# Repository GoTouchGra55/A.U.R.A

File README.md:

# 🚧 Under Active Development 🚧

# 

### A **flight computer** to do met- I mean math for a **rocket** (*Supposedly for a self-landing rocket*).

I had a lot of fun designing this project, though there may still be a few mistakes here and there, so forgive me for that

Feel free to suggest improvements, modify the design, or contribute your own ideas to the project as well!

---

# PCB Preview

### Yes, its 4 layers ;3

---

# Schematics

---

# Extra Info

1. **Use a 2s LiPo battery** if you decide to use this board in your project. **Discard the battery if it smells "funny".**

2. **Check for any damage on the pcb** as it can be the reason for a **catastrophic failure**.

3. **USE A 915MHz SMA ANTENNA ONLY!** Others will work fine but you'll spend a while wondering about the poor range.

---

# Bill Of Materials

### See [BOM](Gravitas-bom.csv)

---

# License

### MIT License - see [LICENSE](LICENSE)

---

# Author

### **Shaurya Tamang**
Contact: shauryatamang.dev@gmail.com

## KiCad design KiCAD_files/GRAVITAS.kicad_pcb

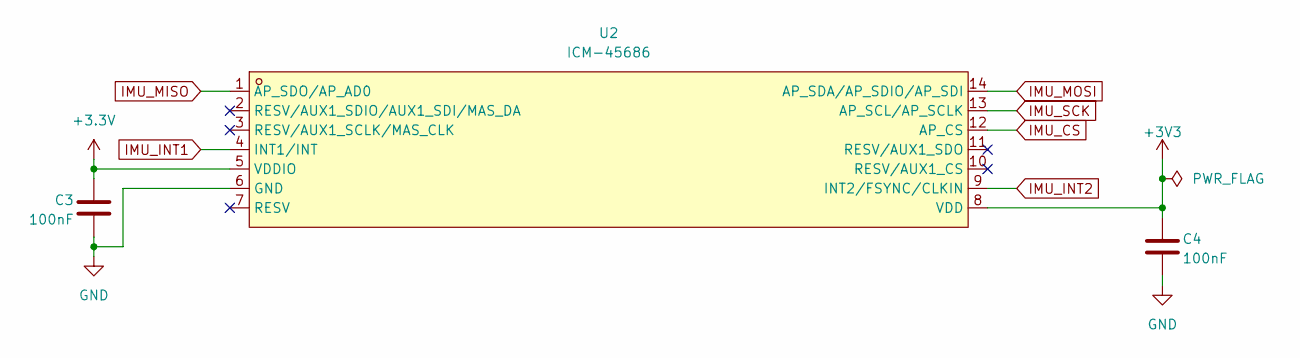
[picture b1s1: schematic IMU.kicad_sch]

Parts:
C3, C4: 100nF; C_0402_1005Metric
U2: ICM-45686; IC_ICM-45686; LCSC Part C22459454

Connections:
+3.3V: C3.1, U2.5 (VDDIO); also elsewhere on the board
+3V3: C4.1, U2.8 (VDD)
IMU_CS: U2.12 (AP_CS); also elsewhere on the board
IMU_INT1: U2.4 (INT1/INT); also elsewhere on the board
IMU_INT2: U2.9 (INT2/FSYNC/CLKIN); also elsewhere on the board
IMU_MISO: U2.1 (AP_SDO/AP_AD0); also elsewhere on the board
IMU_MOSI: U2.14 (AP_SDA/AP_SDIO/AP_SDI); also elsewhere on the board
IMU_SCK: U2.13 (AP_SCL/AP_SCLK); also elsewhere on the board

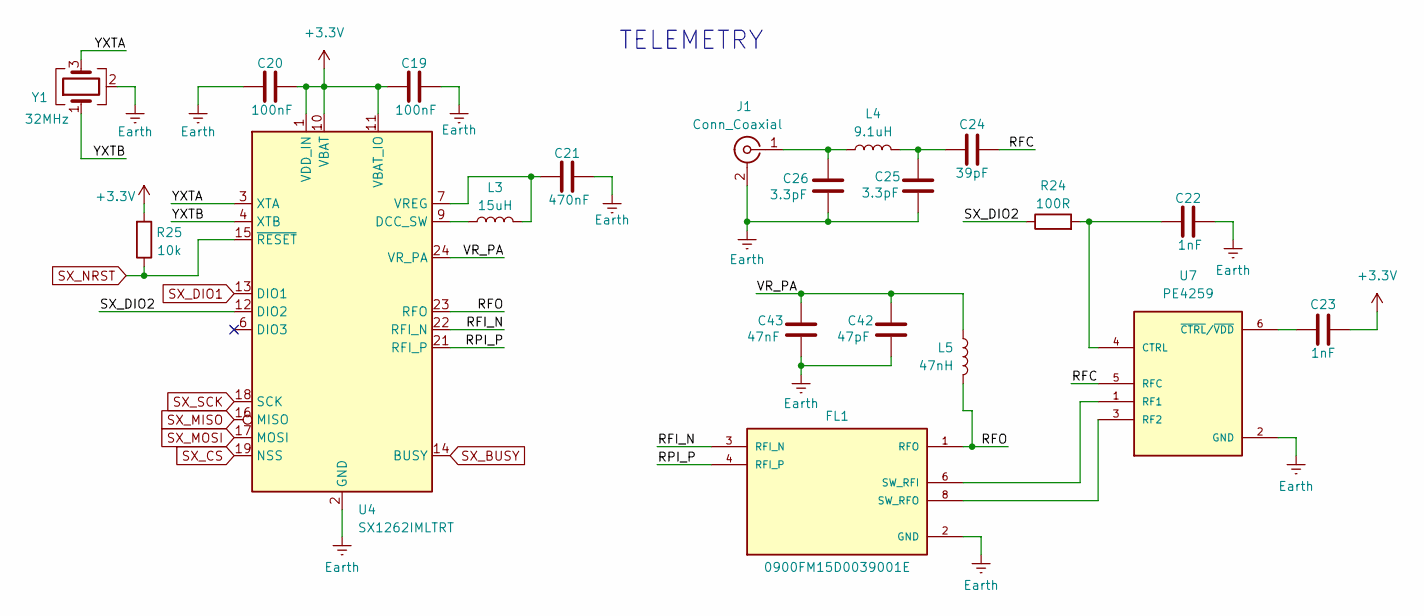
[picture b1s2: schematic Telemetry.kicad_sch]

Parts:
C19, C20: 100nF; C_0402_1005Metric
C21: 470nF; C_0402_1005Metric
C22, C23: 1nF; C_0603_1608Metric
C24: 39pF; C_0402_1005Metric
C25, C26: 3.3pF; C_0402_1005Metric
C42: 47pF; C_0402_1005Metric
C43: 47nF; C_0402_1005Metric
FL1: 0900FM15D0039001E; FIL_0900FM15D0039001E; PARTREV 2.0
J1: Conn_Coaxial; SMA_Amphenol_132134-10_Vertical
L3: 15uH; L_Cenker_CKCS4030
L4: 9.1uH; L_Changjiang_FNR5020S
L5: 47nH; L_0201_0603Metric
R24: 100R; R_0603_1608Metric
R25: 10k; R_0603_1608Metric
U4: SX1262IMLTRT; QFN-24-1EP_4x4mm_P0.5mm_EP2.6x2.6mm
U7: PE4259; SOT65P215X110-6N
Y1: 32MHz; Crystal_SMD_3225-4Pin_3.2x2.5mm

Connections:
+3.3V: C19.1, C20.2, C23.2, R25.2, U4.1 (VDD_IN), U4.10 (VBAT), U4.11 (VBAT_IO); also elsewhere on the board
/Telemetry/RFC: C24.1, U7.5 (RFC)
/Telemetry/RFI_N: FL1.3 (RFI_N), U4.22 (RFI_N)
/Telemetry/RFO: FL1.1 (RFO), L5.1, U4.23 (RFO)
/Telemetry/RPI_P: FL1.4 (RFI_P), U4.21 (RFI_P)
/Telemetry/SX_DIO2: R24.1, U4.12 (DIO2)
/Telemetry/VR_PA: C42.1, C43.1, L5.2, U4.24 (VR_PA)
/Telemetry/YXTA: U4.3 (XTA), Y1.3
/Telemetry/YXTB: U4.4 (XTB), Y1.1
unnamed: C24.2, C25.2, L4.1
unnamed: FL1.6 (SW_RFI), U7.1 (RF1)
unnamed: FL1.8 (SW_RFO), U7.3 (RF2)
unnamed: C26.2, J1.1 (In), L4.2
unnamed: L3.1, U4.9 (DCC_SW)
unnamed: C21.1, L3.2, U4.7 (VREG)
unnamed: C22.1, R24.2, U7.4 (CTRL)
unnamed: C23.1, U7.6 (~CTRL/~VDD)
SX_BUSY: U4.14 (BUSY); also elsewhere on the board
SX_CS: U4.19 (NSS); also elsewhere on the board
SX_DIO1: U4.13 (DIO1); also elsewhere on the board
SX_MISO: U4.16 (MISO); also elsewhere on the board
SX_MOSI: U4.17 (MOSI); also elsewhere on the board
SX_NRST: R25.1, U4.15 (~RESET); also elsewhere on the board
SX_SCK: U4.18 (SCK); also elsewhere on the board

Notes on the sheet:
TELEMETRY

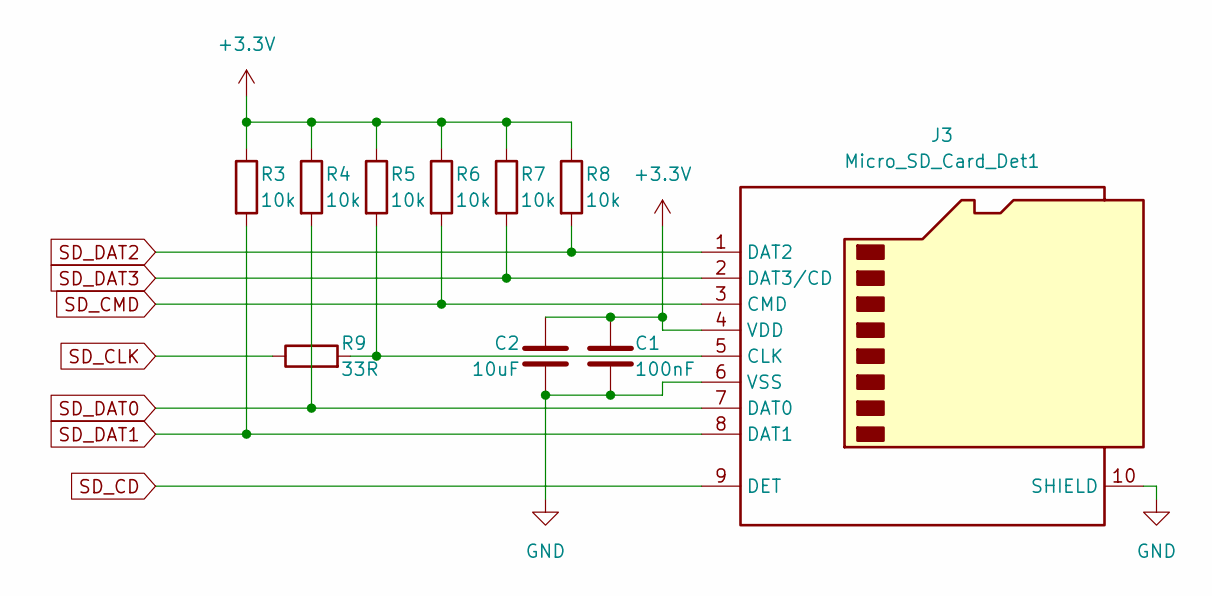
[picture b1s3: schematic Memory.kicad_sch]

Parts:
C1: 100nF; C_0402_1005Metric
C2: 10uF; C_0805_2012Metric
J3: Micro_SD_Card_Det1; microSD_HC_Molex_47219
R3, R4, R5, R6, R7, R8: 10k; R_0603_1608Metric
R9: 33R; R_0603_1608Metric

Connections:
+3.3V: C1.1, C2.1, J3.4 (VDD), R3.1, R4.1, R5.1, R6.1, R7.1, R8.1; also elsewhere on the board
unnamed: J3.5 (CLK), R5.2, R9.2
SD_CD: J3.9 (DET); also elsewhere on the board
SD_CLK: R9.1; also elsewhere on the board
SD_CMD: J3.3 (CMD), R6.2; also elsewhere on the board
SD_DAT0: J3.7 (DAT0), R4.2; also elsewhere on the board
SD_DAT1: J3.8 (DAT1), R3.2; also elsewhere on the board
SD_DAT2: J3.1 (DAT2), R8.2; also elsewhere on the board
SD_DAT3: J3.2 (DAT3/CD), R7.2; also elsewhere on the board

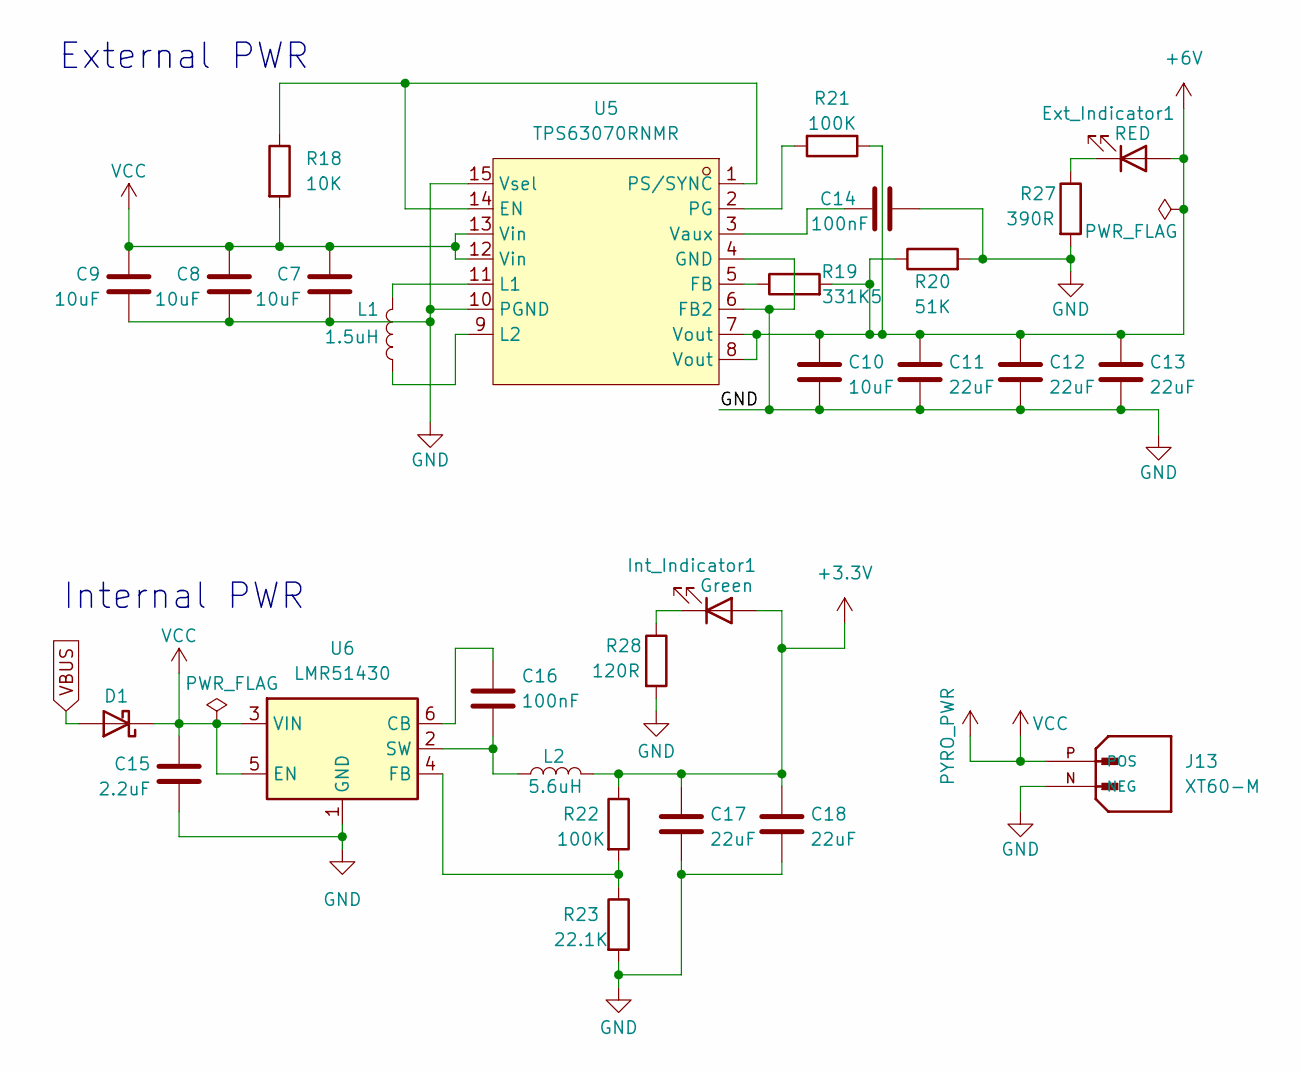
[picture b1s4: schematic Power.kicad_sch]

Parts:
C7, C8, C9, C10: 10uF; C_0805_2012Metric
C11, C12, C13: 22uF; C_0805_2012Metric
C14, C16: 100nF; C_0402_1005Metric
C15: 2.2uF; C_0603_1608Metric
C17, C18: 22uF; C_0603_1608Metric
D1: D_Schottky; D_SOD-123
Ext_Indicator1: RED; LED_0402_1005Metric
Int_Indicator1: Green; LED_0402_1005Metric
J13: XT60-M; AMASS_XT60-M; PARTREV V1.2
L1: 1.5uH; L_Cenker_CKCS4018
L2: 5.6uH; L_Cenker_CKCS3015
R18: 10K; R_0603_1608Metric
R19: 331K5; R_0603_1608Metric
R20: 51K; R_0603_1608Metric
R21, R22: 100K; R_0603_1608Metric
R23: 22.1K; R_0603_1608Metric
R27: 390R; R_0603_1608Metric
R28: 120R; R_0603_1608Metric
U5: TPS63070RNMR; VREG_TPS63070RNMR; LCSC Part C109322
U6: LMR51430; SOT-23-6

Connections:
+3.3V: C17.1, C18.1, Int_Indicator1.2 (A), L2.1, R22.1; also elsewhere on the board
+6V: C10.1, C11.1, C12.1, C13.1, Ext_Indicator1.2 (A), R19.2, R20.1, R21.1, U5.7 (Vout), U5.8 (Vout); also elsewhere on the board
unnamed: Ext_Indicator1.1 (K), R27.1
unnamed: Int_Indicator1.1 (K), R28.1
unnamed: R18.1, U5.1 (PS/SYNC), U5.14 (EN)
unnamed: R19.1, U5.5 (FB)
unnamed: L1.1, U5.11 (L1)
unnamed: L1.2, U5.9 (L2)
unnamed: R21.2, U5.2 (PG)
unnamed: C14.1, U5.3 (Vaux)
unnamed: C16.1, U6.6 (CB)
unnamed: R22.2, R23.1, U6.4 (FB)
unnamed: C16.2, L2.2, U6.2 (SW)
PYRO_PWR: C7.1, C8.1, C9.1, C15.1, D1.1 (K), J13.P (POS), R18.2, U5.12 (Vin), U5.13 (Vin), U6.3 (VIN), U6.5 (EN); also elsewhere on the board
VBUS: D1.2 (A); also elsewhere on the board

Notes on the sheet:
Internal PWR
External PWR

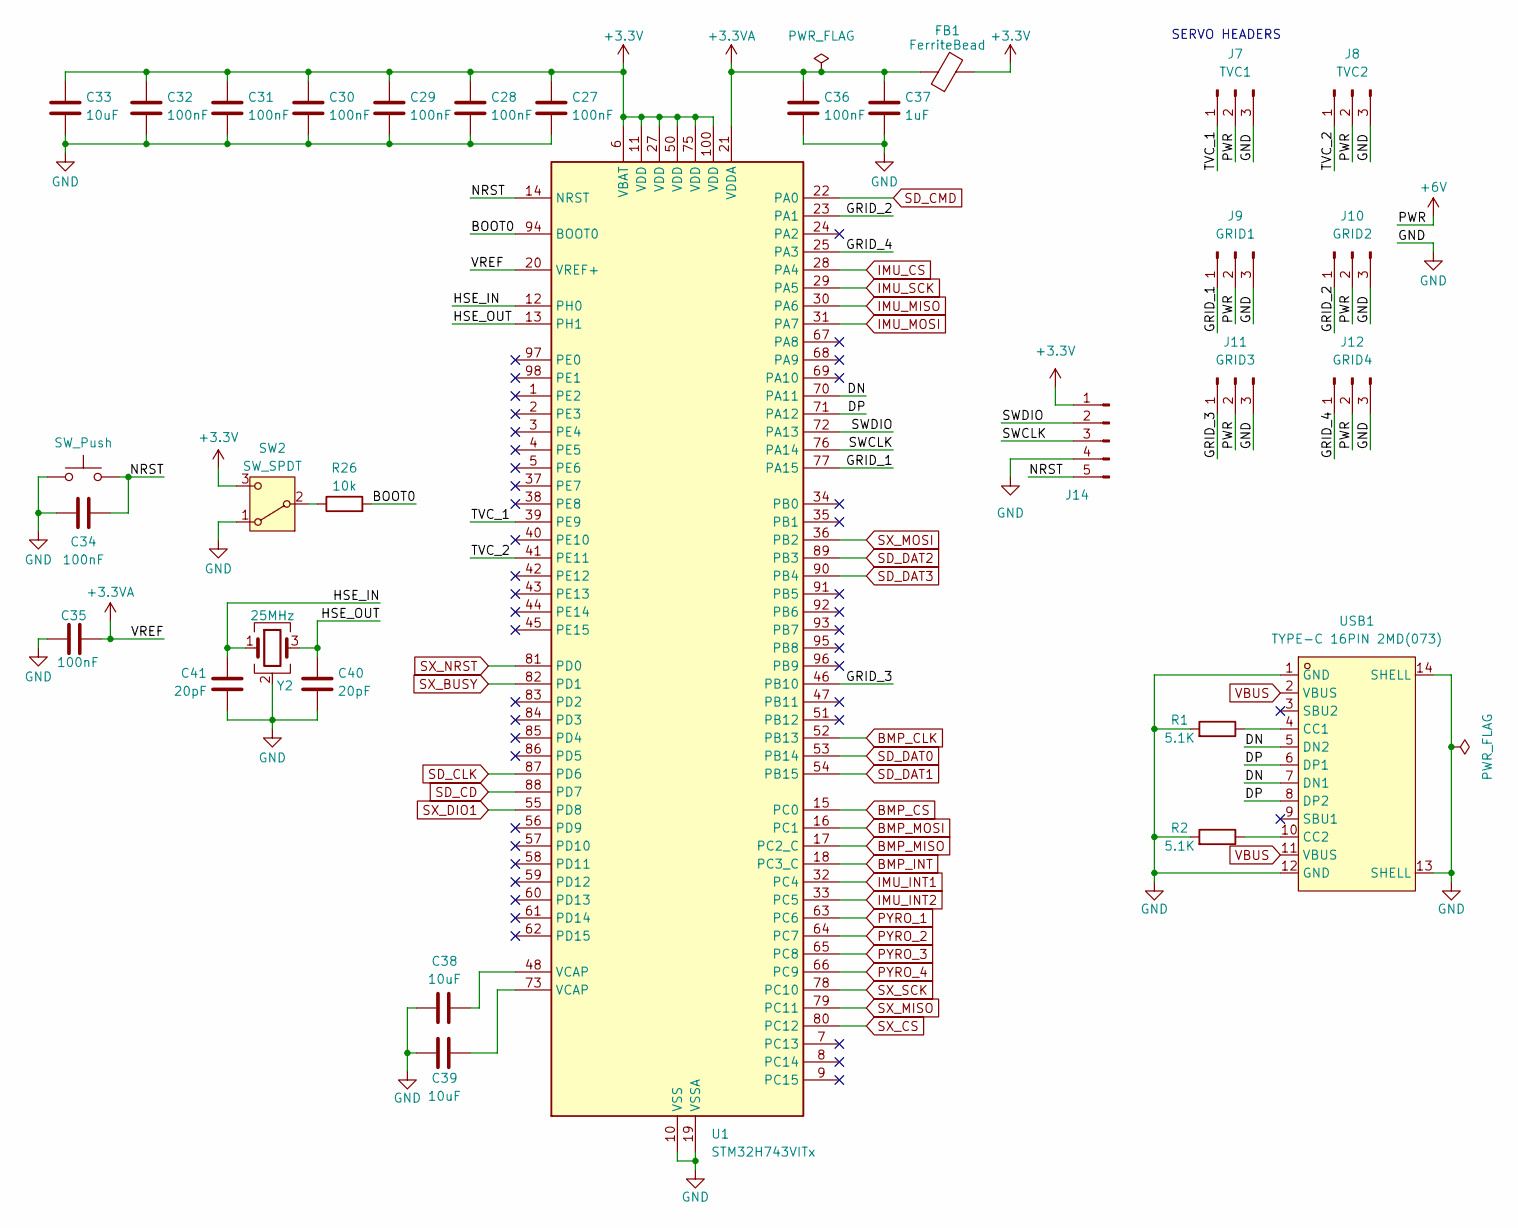
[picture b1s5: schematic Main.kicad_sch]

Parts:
C27, C28, C29, C30, C31, C32, C34, C35, C36: 100nF; C_0402_1005Metric
C33, C38, C39: 10uF; C_0805_2012Metric
C37: 1uF; C_0603_1608Metric
C40, C41: 20pF; C_0402_1005Metric
FB1: FerriteBead; D_0603_1608Metric
J7: TVC1; PinHeader_1x03_P2.54mm_Vertical
J8: TVC2; PinHeader_1x03_P2.54mm_Vertical
J9: GRID1; PinHeader_1x03_P2.54mm_Vertical
J10: GRID2; PinHeader_1x03_P2.54mm_Vertical
J11: GRID3; PinHeader_1x03_P2.54mm_Vertical
J12: GRID4; PinHeader_1x03_P2.54mm_Vertical
J14: Conn_01x05_Pin; JST_EH_S5B-EH_1x05_P2.50mm_Horizontal
R1, R2: 5.1K; R_0603_1608Metric
R26: 10k; R_0603_1608Metric
SW1: SW_Push; SW_SPST_B3S-1000
SW2: SW_SPDT; SW_SPDT_PCM12
U1: STM32H743VITx; LQFP-100_14x14mm_P0.5mm
USB1: TYPE-C 16PIN 2MD(073); HRO_TYPE-C-31-M-12; LCSC Part C2765186
Y2: 25MHz; Crystal_SMD_3225-4Pin_3.2x2.5mm

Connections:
+3.3V: C27.1, C28.1, C29.1, C30.1, C31.1, C32.1, C33.1, FB1.2, J14.1, SW2.3 (C), U1.6 (VBAT), U1.11 (VDD), U1.27 (VDD), U1.50 (VDD), U1.75 (VDD), U1.100 (VDD); also elsewhere on the board
+3.3VA: C35.1, C36.1, C37.1, FB1.1, U1.20 (VREF+), U1.21 (VDDA)
+6V: J7.2, J8.2, J9.2, J10.2, J11.2, J12.2; also elsewhere on the board
/MCU/BOOT0: R26.2, U1.94 (BOOT0)
/MCU/DN: U1.70 (PA11), USB1.5 (DN2), USB1.7 (DN1)
/MCU/DP: U1.71 (PA12), USB1.6 (DP1), USB1.8 (DP2)
/MCU/GRID_1: J9.1, U1.77 (PA15); also elsewhere on the board
/MCU/GRID_2: J10.1, U1.23 (PA1)
/MCU/GRID_3: J11.1, U1.46 (PB10)
/MCU/GRID_4: J12.1, U1.25 (PA3)
/MCU/HSE_IN: C41.1, U1.12 (PH0), Y2.1
/MCU/HSE_OUT: C40.1, U1.13 (PH1), Y2.3
/MCU/NRST: C34.1, J14.5, SW1.2, U1.14 (NRST)
/MCU/SWCLK: J14.3, U1.76 (PA14)
/MCU/SWDIO: J14.2, U1.72 (PA13)
/MCU/TVC_1: J7.1, U1.39 (PE9); also elsewhere on the board
/MCU/TVC_2: J8.1, U1.41 (PE11); also elsewhere on the board
BMP_CLK: U1.52 (PB13); also elsewhere on the board
BMP_CS: U1.15 (PC0); also elsewhere on the board
BMP_INT: U1.18 (PC3_C); also elsewhere on the board
BMP_MISO: U1.17 (PC2_C); also elsewhere on the board
BMP_MOSI: U1.16 (PC1); also elsewhere on the board
IMU_CS: U1.28 (PA4); also elsewhere on the board
IMU_INT1: U1.32 (PC4); also elsewhere on the board
IMU_INT2: U1.33 (PC5); also elsewhere on the board
IMU_MISO: U1.30 (PA6); also elsewhere on the board
IMU_MOSI: U1.31 (PA7); also elsewhere on the board
IMU_SCK: U1.29 (PA5); also elsewhere on the board
unnamed: C38.2, U1.48 (VCAP)
unnamed: C39.1, U1.73 (VCAP)
unnamed: R26.1, SW2.2 (B)
unnamed: R1.1, USB1.4 (CC1)
unnamed: R2.1, USB1.10 (CC2)
PYRO_1: U1.63 (PC6); also elsewhere on the board
PYRO_2: U1.64 (PC7); also elsewhere on the board
PYRO_3: U1.65 (PC8); also elsewhere on the board
PYRO_4: U1.66 (PC9); also elsewhere on the board
SD_CD: U1.88 (PD7); also elsewhere on the board
SD_CLK: U1.87 (PD6); also elsewhere on the board
SD_CMD: U1.22 (PA0); also elsewhere on the board
SD_DAT0: U1.53 (PB14); also elsewhere on the board
SD_DAT1: U1.54 (PB15); also elsewhere on the board
SD_DAT2: U1.89 (PB3); also elsewhere on the board
SD_DAT3: U1.90 (PB4); also elsewhere on the board
SX_BUSY: U1.82 (PD1); also elsewhere on the board
SX_CS: U1.80 (PC12); also elsewhere on the board
SX_DIO1: U1.55 (PD8); also elsewhere on the board
SX_MISO: U1.79 (PC11); also elsewhere on the board
SX_MOSI: U1.36 (PB2); also elsewhere on the board
SX_NRST: U1.81 (PD0); also elsewhere on the board
SX_SCK: U1.78 (PC10); also elsewhere on the board
VBUS: USB1.2 (VBUS), USB1.11 (VBUS); also elsewhere on the board

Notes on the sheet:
SERVO HEADERS

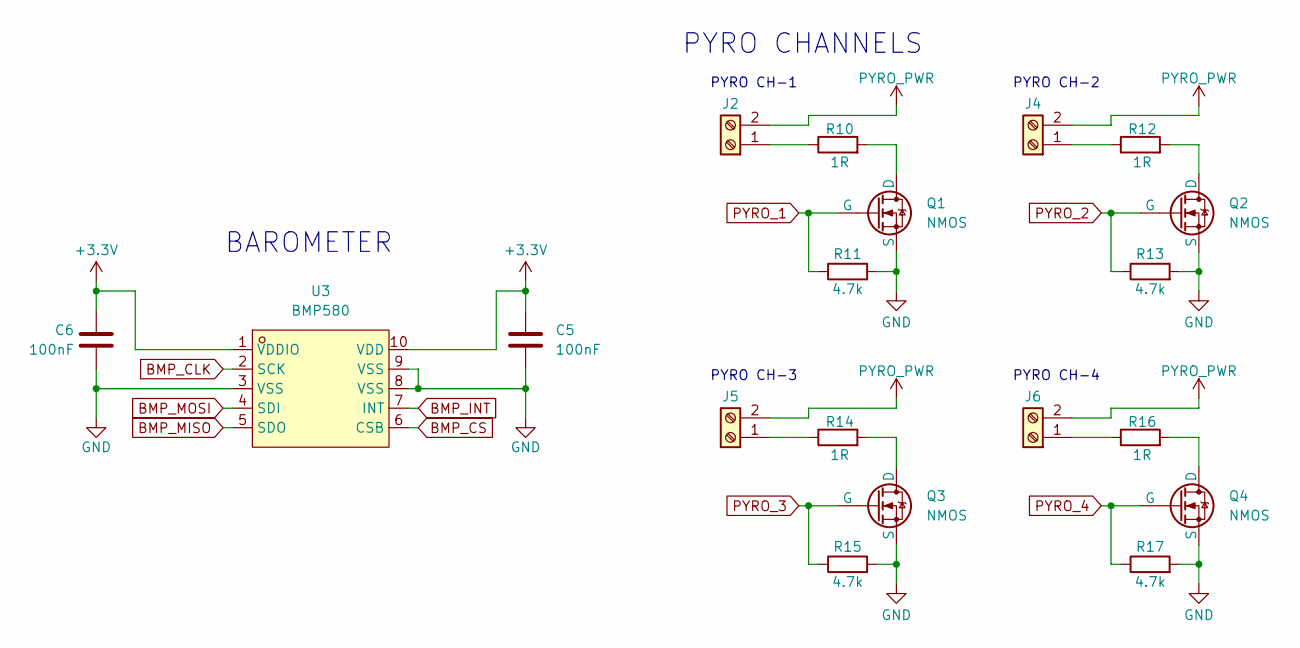
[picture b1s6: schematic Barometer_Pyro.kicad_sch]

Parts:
C5, C6: 100nF; C_0402_1005Metric
J2, J4, J5, J6: Screw_Terminal_01x02; TerminalBlock_Phoenix_MKDS-1-2-3.81_1x02_P3.81mm_Horizontal
Q1, Q2, Q3, Q4: NMOS; TRANS_IRLML6344TRPBF
R10, R12, R14, R16: 1R; R_0603_1608Metric
R11, R13, R15, R17: 4.7k; R_0603_1608Metric
U3: BMP580; ST_HLGA-10_2x2mm_P0.5mm_LayoutBorder3x2y; LCSC Part C22391138

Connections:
+3.3V: C5.1, C6.1, U3.1 (VDDIO), U3.10 (VDD); also elsewhere on the board
BMP_CLK: U3.2 (SCK); also elsewhere on the board
BMP_CS: U3.6 (CSB); also elsewhere on the board
BMP_INT: U3.7 (INT); also elsewhere on the board
BMP_MISO: U3.5 (SDO); also elsewhere on the board
BMP_MOSI: U3.4 (SDI); also elsewhere on the board
unnamed: J2.1, R10.1
unnamed: J4.1, R12.1
unnamed: J5.1, R14.1
unnamed: J6.1, R16.1
unnamed: Q1.1 (D), R10.2
unnamed: Q2.1 (D), R12.2
unnamed: Q3.1 (D), R14.2
unnamed: Q4.1 (D), R16.2
PYRO_1: Q1.2 (G), R11.1; also elsewhere on the board
PYRO_2: Q2.2 (G), R13.1; also elsewhere on the board
PYRO_3: Q3.2 (G), R15.1; also elsewhere on the board
PYRO_4: Q4.2 (G), R17.1; also elsewhere on the board
PYRO_PWR: J2.2, J4.2, J5.2, J6.2; also elsewhere on the board

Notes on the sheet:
PYRO CHANNELS
PYRO CH-3
PYRO CH-4
BAROMETER
PYRO CH-2
PYRO CH-1

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
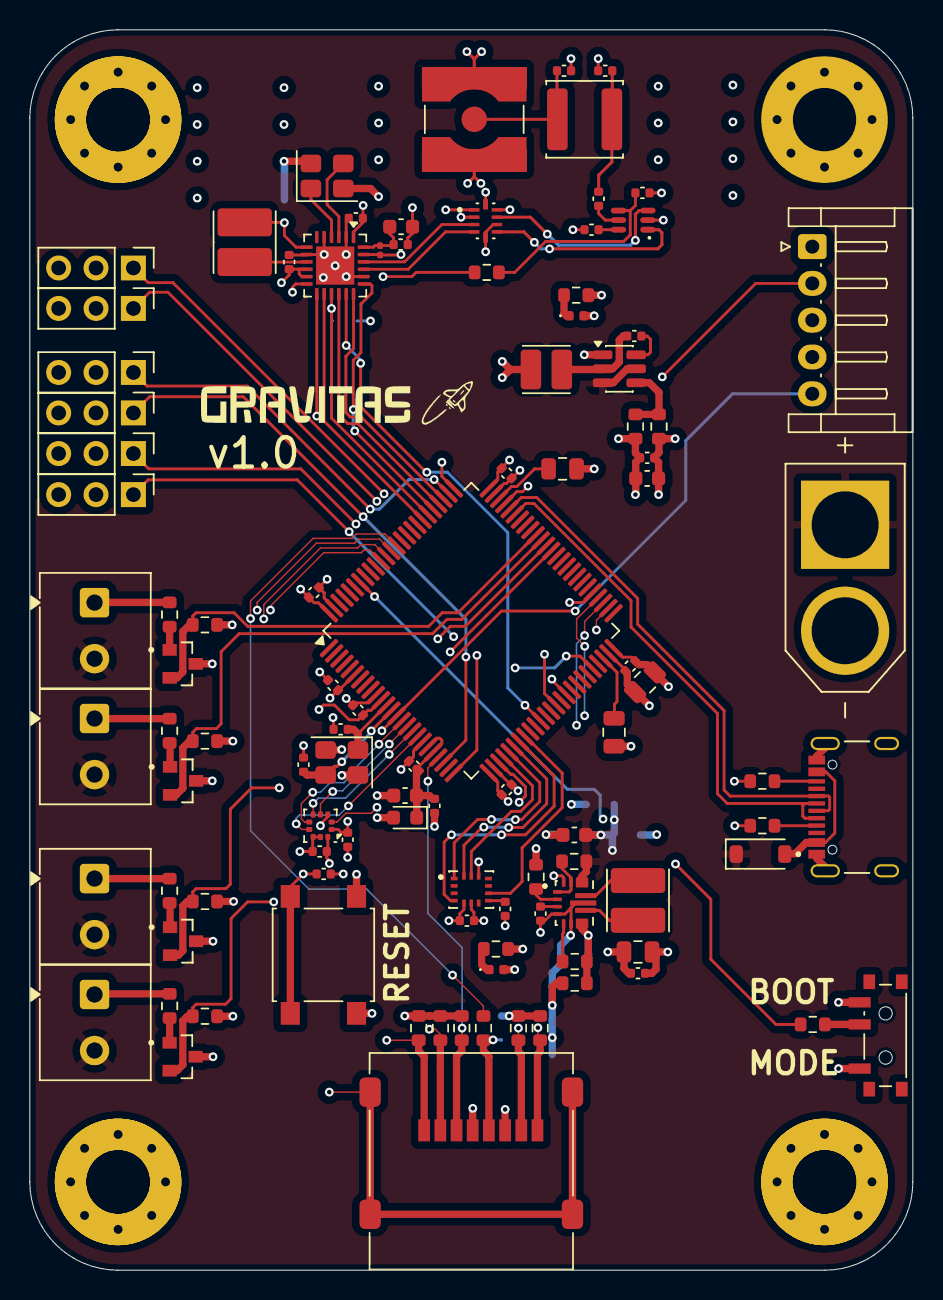
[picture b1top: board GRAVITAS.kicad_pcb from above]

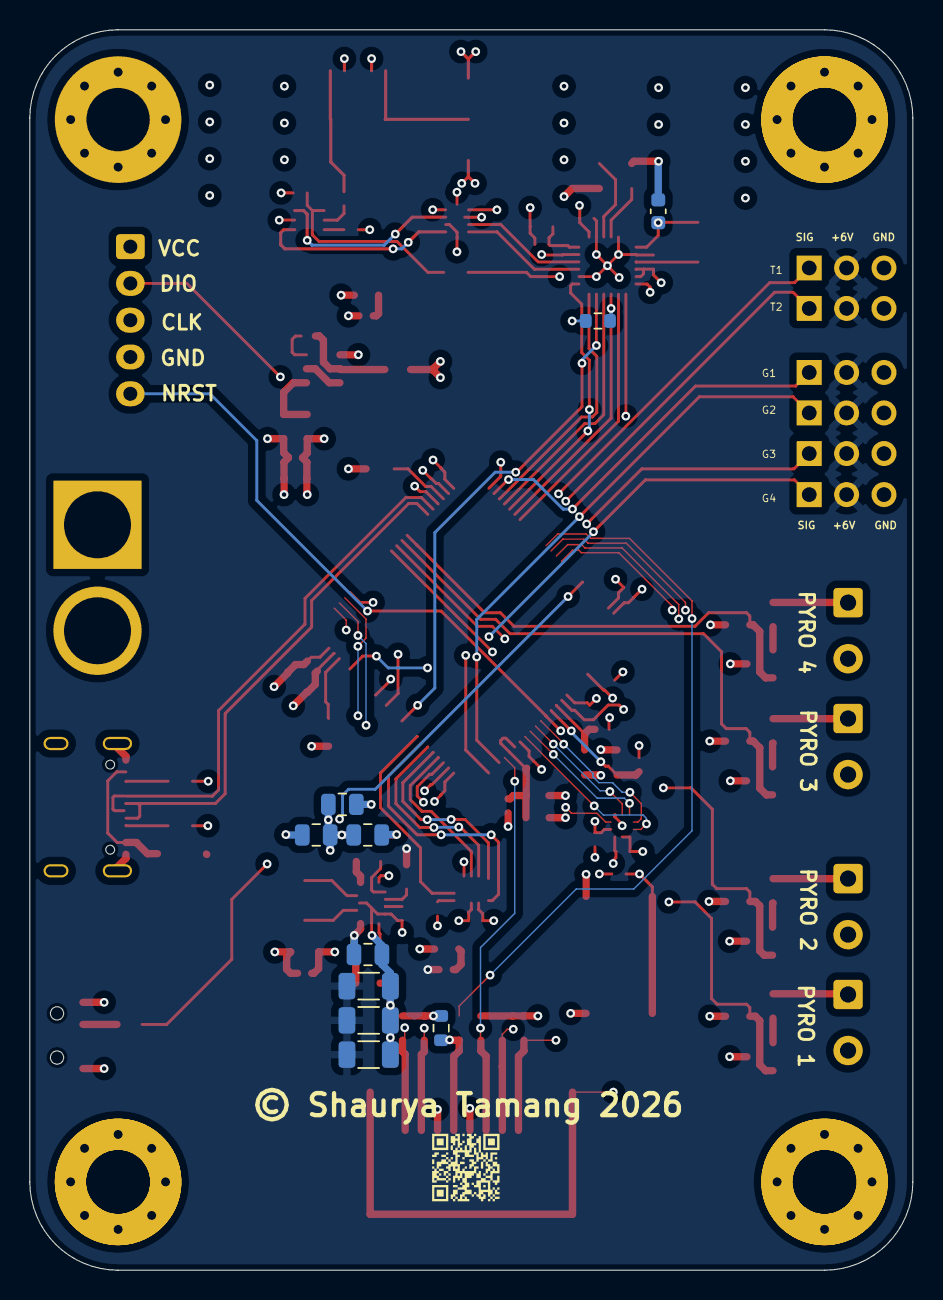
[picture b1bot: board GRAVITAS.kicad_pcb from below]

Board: 4 copper layers, 60.0 x 84.3 mm, 111 parts (10 on the bottom side), 91 nets.

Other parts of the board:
G1: GRID1; PinHeader_1x03_P2.54mm_Vertical
T1: TVC1; PinHeader_1x03_P2.54mm_Vertical
T2: TVC2; PinHeader_1x03_P2.54mm_Vertical

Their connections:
+6V: G1.2, T1.2, T2.2; also elsewhere on the board
/MCU/GRID_1: G1.1; also elsewhere on the board
/MCU/TVC_1: T1.1; also elsewhere on the board
/MCU/TVC_2: T2.1; also elsewhere on the board

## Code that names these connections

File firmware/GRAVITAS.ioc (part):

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Mcu.Name=STM32H743VITx
Mcu.Package=LQFP100
Mcu.UserName=STM32H743VITx
PA0.Mode=SD_4_bits_Wide_bus
PA0.Signal=SDMMC2_CMD
PA1.GPIOParameters=GPIO_Label
PA1.GPIO_Label=GRID_CH2
PA1.Signal=S_TIM2_CH2
PA11.Mode=Host_Only
PA11.Signal=USB_OTG_FS_DM
PA12.Mode=Host_Only
PA12.Signal=USB_OTG_FS_DP
PA13\ (JTMS/SWDIO).Mode=Serial_Wire
PA13\ (JTMS/SWDIO).Signal=DEBUG_JTMS-SWDIO
PA14\ (JTCK/SWCLK).Mode=Serial_Wire
PA14\ (JTCK/SWCLK).Signal=DEBUG_JTCK-SWCLK
PA15\ (JTDI).GPIOParameters=GPIO_Label
PA15\ (JTDI).GPIO_Label=GRID_CH1
PA15\ (JTDI).Signal=S_TIM2_CH1_ETR
PA3.GPIOParameters=GPIO_Label
PA3.GPIO_Label=GRID_CH4
PA3.Signal=S_TIM2_CH4
PA4.GPIOParameters=GPIO_Label
PA4.GPIO_Label=IMU_CS
PA4.Signal=GPIO_Output
PA5.GPIOParameters=GPIO_Label
PA5.GPIO_Label=IMU_SCK
PA5.Mode=Full_Duplex_Master
PA5.Signal=SPI1_SCK
PA6.GPIOParameters=GPIO_Label
PA6.GPIO_Label=IMU_MISO
PA6.Mode=Full_Duplex_Master
PA6.Signal=SPI1_MISO
PA7.GPIOParameters=GPIO_Label
PA7.GPIO_Label=IMU_MOSI
PA7.Mode=Full_Duplex_Master
PA7.Signal=SPI1_MOSI
PB10.GPIOParameters=GPIO_Label
PB10.GPIO_Label=GRID_CH3
PB10.Signal=S_TIM2_CH3
PB13.GPIOParameters=GPIO_Label
PB13.GPIO_Label=BMP_SCK
PB13.Mode=Full_Duplex_Master
PB13.Signal=SPI2_SCK
PB14.Mode=SD_4_bits_Wide_bus
PB14.Signal=SDMMC2_D0
PB15.Mode=SD_4_bits_Wide_bus
PB15.Signal=SDMMC2_D1
PB2.GPIOParameters=GPIO_Label
PB2.GPIO_Label=SX_MOSI
PB2.Mode=Full_Duplex_Master
PB2.Signal=SPI3_MOSI
PB3\ (JTDO/TRACESWO).Mode=SD_4_bits_Wide_bus
PB3\ (JTDO/TRACESWO).Signal=SDMMC2_D2
PB4\ (NJTRST).Mode=SD_4_bits_Wide_bus
PB4\ (NJTRST).Signal=SDMMC2_D3
PC0.GPIOParameters=GPIO_Label
PC0.GPIO_Label=BMP_CS
PC0.Signal=GPIO_Output
PC1.GPIOParameters=GPIO_Label
PC1.GPIO_Label=BMP_MOSI
PC1.Mode=Full_Duplex_Master
PC1.Signal=SPI2_MOSI
PC10.GPIOParameters=GPIO_Label
PC10.GPIO_Label=SX_SCK
PC10.Mode=Full_Duplex_Master
PC10.Signal=SPI3_SCK
PC11.GPIOParameters=GPIO_Label
PC11.GPIO_Label=SX_MISO
PC11.Mode=Full_Duplex_Master
PC11.Signal=SPI3_MISO
PC12.GPIOParameters=GPIO_Label
PC12.GPIO_Label=SX_CS
PC12.Signal=GPIO_Output
PC2_C.GPIOParameters=GPIO_Label
PC2_C.GPIO_Label=BMP_MISO
PC2_C.Mode=Full_Duplex_Master
PC2_C.Signal=SPI2_MISO
PC3_C.GPIOParameters=GPIO_Label
PC3_C.GPIO_Label=BMP_INT
PC3_C.Signal=GPXTI3
PC4.GPIOParameters=GPIO_Label
PC4.GPIO_Label=IMU_INT1
PC4.Signal=GPXTI4
PC5.GPIOParameters=GPIO_Label
PC5.GPIO_Label=IMU_INT2
PC5.Signal=GPXTI5
PC6.GPIOParameters=GPIO_Label
PC6.GPIO_Label=PYRO_CH1
PC6.Signal=GPIO_Output
PC7.GPIOParameters=GPIO_Label
PC7.GPIO_Label=PYRO_CH2
PC7.Signal=GPIO_Output
PC8.GPIOParameters=GPIO_Label
PC8.GPIO_Label=PYRO_CH3
PC8.Signal=GPIO_Output
PC9.GPIOParameters=GPIO_Label
PC9.GPIO_Label=PYRO_CH4
PC9.Signal=GPIO_Output
PD0.GPIOParameters=PinState,GPIO_Label
PD0.GPIO_Label=SX_NRST
PD0.PinState=GPIO_PIN_SET
PD0.Signal=GPIO_Output
PD1.GPIOParameters=GPIO_Label
PD1.GPIO_Label=SX_BUSY
PD1.Signal=GPIO_Input
PD6.Mode=SD_4_bits_Wide_bus
PD6.Signal=SDMMC2_CK
PD7.GPIOParameters=GPIO_Label
PD7.GPIO_Label=SD_CD
PD7.Signal=GPIO_Input
PE11.GPIOParameters=GPIO_Label
PE11.GPIO_Label=TVC_CH2
PE11.Signal=S_TIM1_CH2
PE9.GPIOParameters=GPIO_Label
PE9.GPIO_Label=TVC_CH1
PE9.Signal=S_TIM1_CH1
PH0-OSC_IN\ (PH0).Mode=HSE-External-Oscillator
PH0-OSC_IN\ (PH0).Signal=RCC_OSC_IN
PH1-OSC_OUT\ (PH1).Mode=HSE-External-Oscillator
PH1-OSC_OUT\ (PH1).Signal=RCC_OSC_OUT
RCC.SYSCLKFreq_VALUE=64000000
board=custom

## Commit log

2026-05-02 Add firmware init files
2026-05-10 Rename project from A.U.R.A to GRAVITAS
2026-05-10 Add firmware files for GRAVITAS
2026-05-11 Add KiCAD files
2026-05-11 Add images
2026-05-11 Update README and add files

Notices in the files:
KiCAD_files/GRAVITAS.kicad_pcb:
© Shaurya Tamang 2026
